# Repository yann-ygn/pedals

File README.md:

# pedals

A collection of guitar effects pcbs made with Eagle.

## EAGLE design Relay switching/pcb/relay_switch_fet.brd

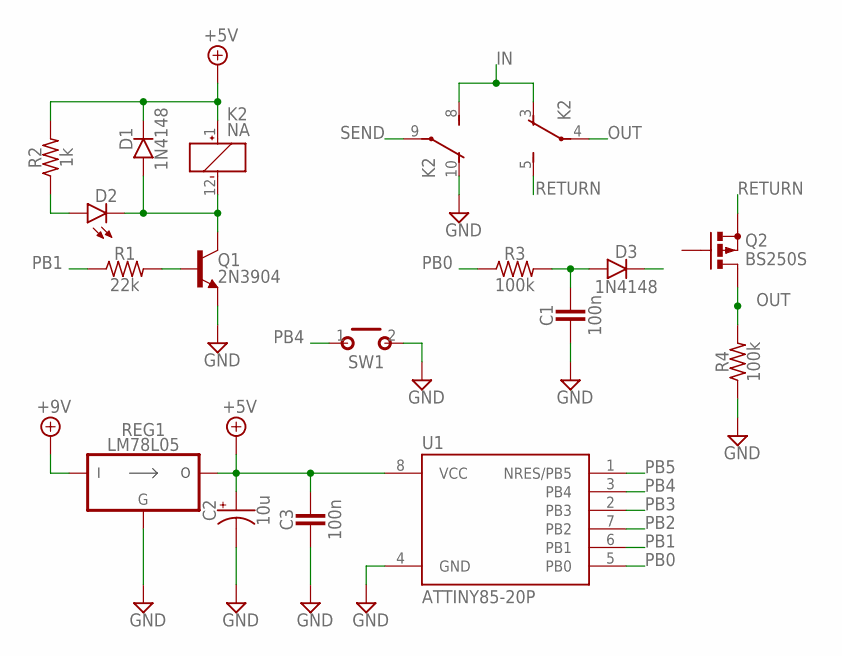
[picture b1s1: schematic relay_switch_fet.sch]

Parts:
C1: 100n; BOX_SMALL
C2: 10u; 050_020
C3: 100n; 050X030_025_2
D1, D3: 1N4148; DO35-2
D2: LED; 3MM_D
K2: NA
Q1: 2N3904; TO92-
Q2: BS250S; SOT54ES
R1: 22k; R0207/3
R2: 1k; R0207/3
R3, R4: 100k; R0207/3
REG1: LM78L05; TO92-
SW1: MOMENTARY; SPST
U1: ATTINY85-20P; PDIP08_300MIL

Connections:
+5V: C2.+, C3.1, D1.C, K2.1 (+), R2.2, REG1.3 (VO), U1.8 (VCC)
+9V: REG1.1 (VI)
GND: C1.2, C2.-, C3.2, K2.10 (O), Q1.3 (E), R4.1, REG1.2 (GND), SW1.2 (S), U1.4 (GND)
IN: K2.3 (O), K2.8 (S)
unnamed: D1.A, D2.P$1 (C), K2.12 (-), Q1.1 (C)
unnamed: Q1.2 (B), R1.2
unnamed: D2.ANODE (A), R2.1
unnamed: C1.1, D3.A, R3.2
OUT: K2.4, Q2.D, R4.2
PB0: R3.1, U1.5 (PB0)
PB1: R1.1, U1.6 (PB1)
PB2: U1.7 (PB2)
PB3: U1.2 (PB3)
PB4: SW1.1, U1.3 (PB4)
PB5: U1.1 (NRES/PB5)
RETURN: K2.5 (S), Q2.S
SEND: K2.9

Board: 2 copper layers, 15 parts (0 on the bottom side), 11 nets, no tracks yet.

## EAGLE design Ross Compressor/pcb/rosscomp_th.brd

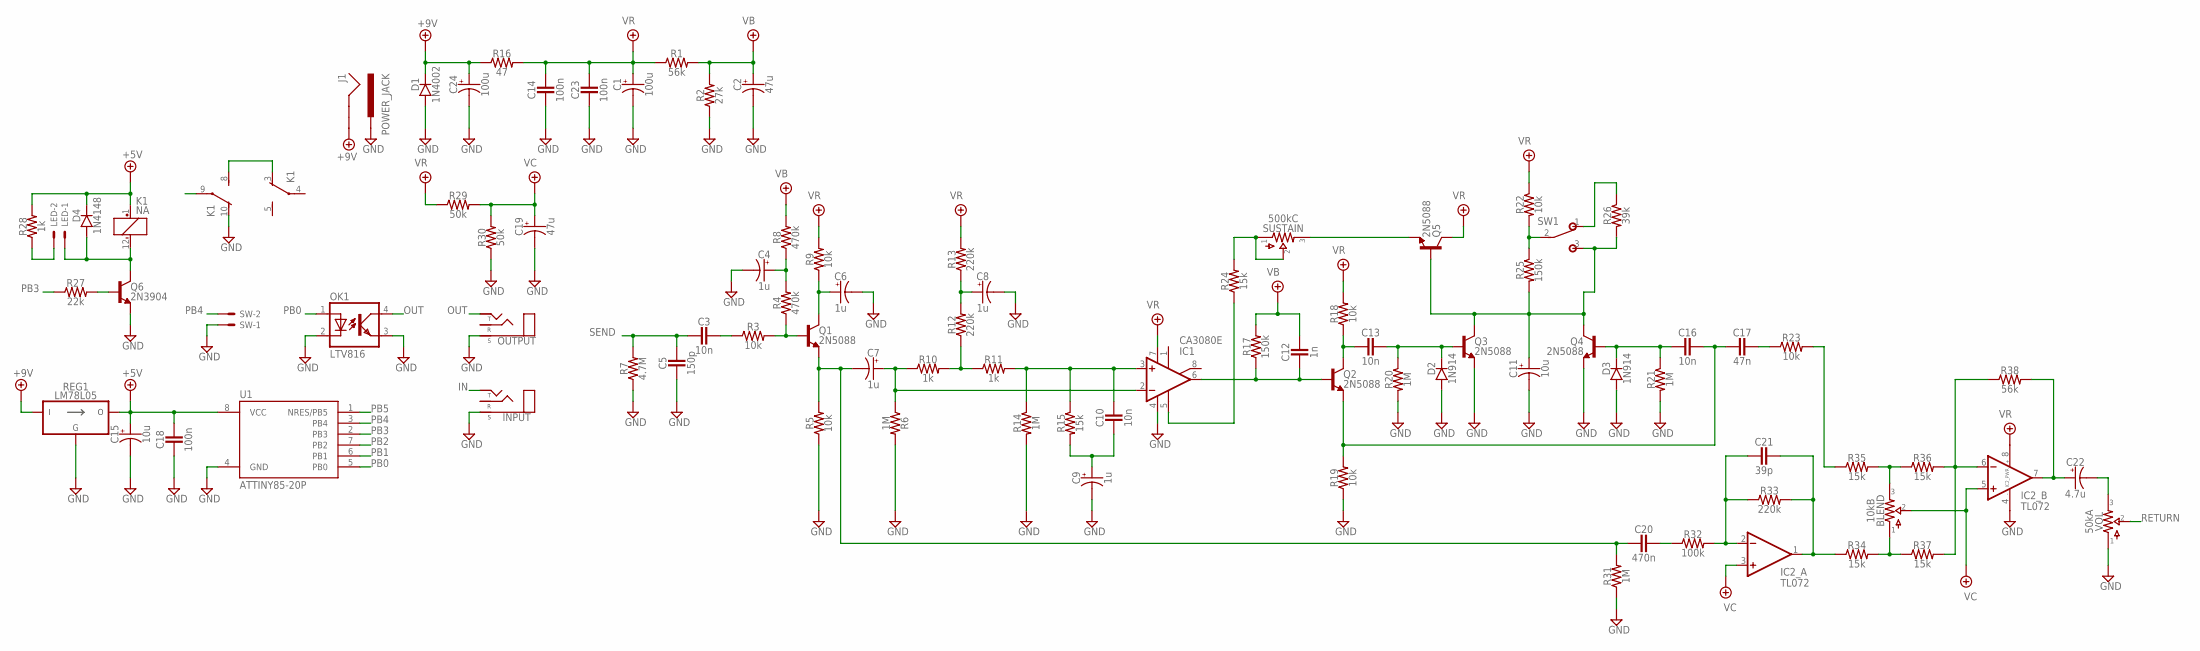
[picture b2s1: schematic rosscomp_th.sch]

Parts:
BLEND: 10kB; 16MM
C1, C24: 100u; 050_020
C2, C19: 47u; 050_020
C3, C10, C13, C16: 10n; BOX_SMALL
C4, C6, C7, C8, C9: 1u; 040_020
C5: 150p; 050X030_025_2
C11, C15: 10u; 050_020
C12: 1n; BOX_SMALL
C14, C18, C23: 100n; 050X030_025_2
C17: 47n; BOX_SMALL
C20: 470n; BOX_MED
C21: 39p; 050X030_025_2
C22: 4.7u; 050_020
D1: 1N4002; DO41-2
D2, D3: 1N914; DO35-2
D4: 1N4148; DO35-2
IC1: CA3080E; DIL0
IC2: TL072; DIL0
INPUT: STEREONMJ; NMJ6HCD2
J1: POWER_JACK; POWER_JACK_PTH
K1: NA
LED: JST-XH-02-PIN-ROUND-PAD; JST-XH-02-PACKAGE-ROUND-PAD
OK1: LTV816; DIL04
OUTPUT: STEREONMJ; NMJ6HCD2
Q1, Q2, Q3, Q4, Q5: 2N5088; TO92-
Q6: 2N3904; TO92-
R1, R38: 56k; R0207/3
R2: 27k; R0207/3
R3, R5, R9, R18, R19, R22, R23: 10k; R0207/3
R4, R8: 470k; R0207/3
R6, R14, R20, R21, R31: 1M; R0207/3
R7: 4.7M; R0207/3
R10, R11, R28: 1k; R0207/3
R12, R13, R33: 220k; R0207/3
R15, R24, R34, R35, R36, R37: 15k; R0207/3
R16: 47; R0207/3
R17, R25: 150k; R0207/3
R26: 39k; R0207/3
R27: 22k; R0207/3
R29, R30: 50k; R0207/3
R32: 100k; R0207/3
REG1: LM78L05; TO92-
SUSTAIN: 500kC; 16MM
SW: JST-XH-02-PIN-ROUND-PAD; JST-XH-02-PACKAGE-ROUND-PAD
SW1: SPDT; M9040P
U1: ATTINY85-20P; PDIP08_300MIL
VOL: 50kA; 16MM

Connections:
+5V: C15.+, C18.1, D4.C, K1.1 (+), R28.2, REG1.3 (VO), U1.8 (VCC)
+9V: C24.+, D1.C, J1.GND, R16.1, REG1.1 (VI)
GND: C1.-, C2.-, C4.-, C5.2, C6.-, C8.-, C9.-, C11.-, C14.1, C15.-, C18.2, C19.-, C23.1, C24.-, D1.A, D2.A, D3.A, IC1.4 (V-), IC2.4 (V-), INPUT.S, J1.PWR, K1.10 (O), OK1.2 (C), OK1.3 (EMIT), OUTPUT.S, Q3.3 (E), Q4.3 (E), Q6.3 (E), R2.1, R5.1, R6.2, R7.1, R14.2, R19.1, R20.2, R21.2, R30.1, R31.1, REG1.2 (GND), SW.1, U1.4 (GND), VOL.1
IN: INPUT.T
unnamed: D4.A, K1.12 (-), LED.1, Q6.1 (C)
unnamed: C3.1, R3.1
unnamed: Q1.2 (B), R3.2, R4.1
unnamed: Q6.2 (B), R27.2
unnamed: C4.+, R4.2, R8.1
unnamed: R26.1, SW1.1 (O)
unnamed: C6.+, Q1.1 (C), R9.1
unnamed: C7.+, IC1.2 (-IN), R6.1, R10.1
unnamed: C7.-, C20.2, Q1.3 (E), R5.2, R31.2
unnamed: C10.1, IC1.3 (+IN), R11.2, R14.1, R15.1
unnamed: R10.2, R11.1, R12.1
unnamed: C8.+, R12.2, R13.1
unnamed: C9.+, C10.2, R15.2
unnamed: C13.2, Q2.1 (C), R18.1
unnamed: C12.2, IC1.6 (OUT), Q2.2 (B), R17.1
unnamed: C16.1, C17.2, Q2.3 (E), R19.2
unnamed: C13.1, D2.C, Q3.2 (B), R20.1
unnamed: C11.+, Q3.1 (C), Q4.1 (C), Q5.2 (B), R25.2, R26.2, SW1.3 (S)
unnamed: C16.2, D3.C, Q4.2 (B), R21.1
unnamed: R22.2, R25.1, SW1.2
unnamed: C17.1, R23.1
unnamed: C20.1, R32.1
unnamed: Q5.3 (E), SUSTAIN.3
unnamed: LED.2, R28.1
unnamed: R24.2, SUSTAIN.1, SUSTAIN.2
unnamed: IC1.5 (OPT), R24.1
unnamed: K1.3 (O), K1.8 (S)
unnamed: C21.2, IC2.2 (-IN), R32.2, R33.1
unnamed: C21.1, IC2.1 (OUT), R33.2, R34.1
unnamed: BLEND.1, R34.2, R37.1
unnamed: BLEND.3, R35.2, R36.1
unnamed: R23.2, R35.1
unnamed: C22.+, IC2.7 (OUT), R38.2
unnamed: C22.-, VOL.3
unnamed: IC2.6 (-IN), R36.2, R37.2, R38.1
OUT: OK1.4 (COL), OUTPUT.T
PB0: OK1.1 (A), U1.5 (PB0)
PB1: U1.6 (PB1)
PB2: U1.7 (PB2)
PB3: R27.1, U1.2 (PB3)
PB4: SW.2, U1.3 (PB4)
PB5: U1.1 (NRES/PB5)
RETURN: VOL.2
SEND: C3.2, C5.1, R7.2
VB: C2.+, C12.1, R1.2, R2.2, R8.2, R17.2
VC: BLEND.2, C19.+, IC2.3 (+IN), IC2.5 (+IN), R29.2, R30.2
VR: C1.+, C14.2, C23.2, IC1.7 (V+), IC2.8 (V+), Q5.1 (C), R1.1, R9.2, R13.2, R16.2, R18.2, R22.1, R29.1

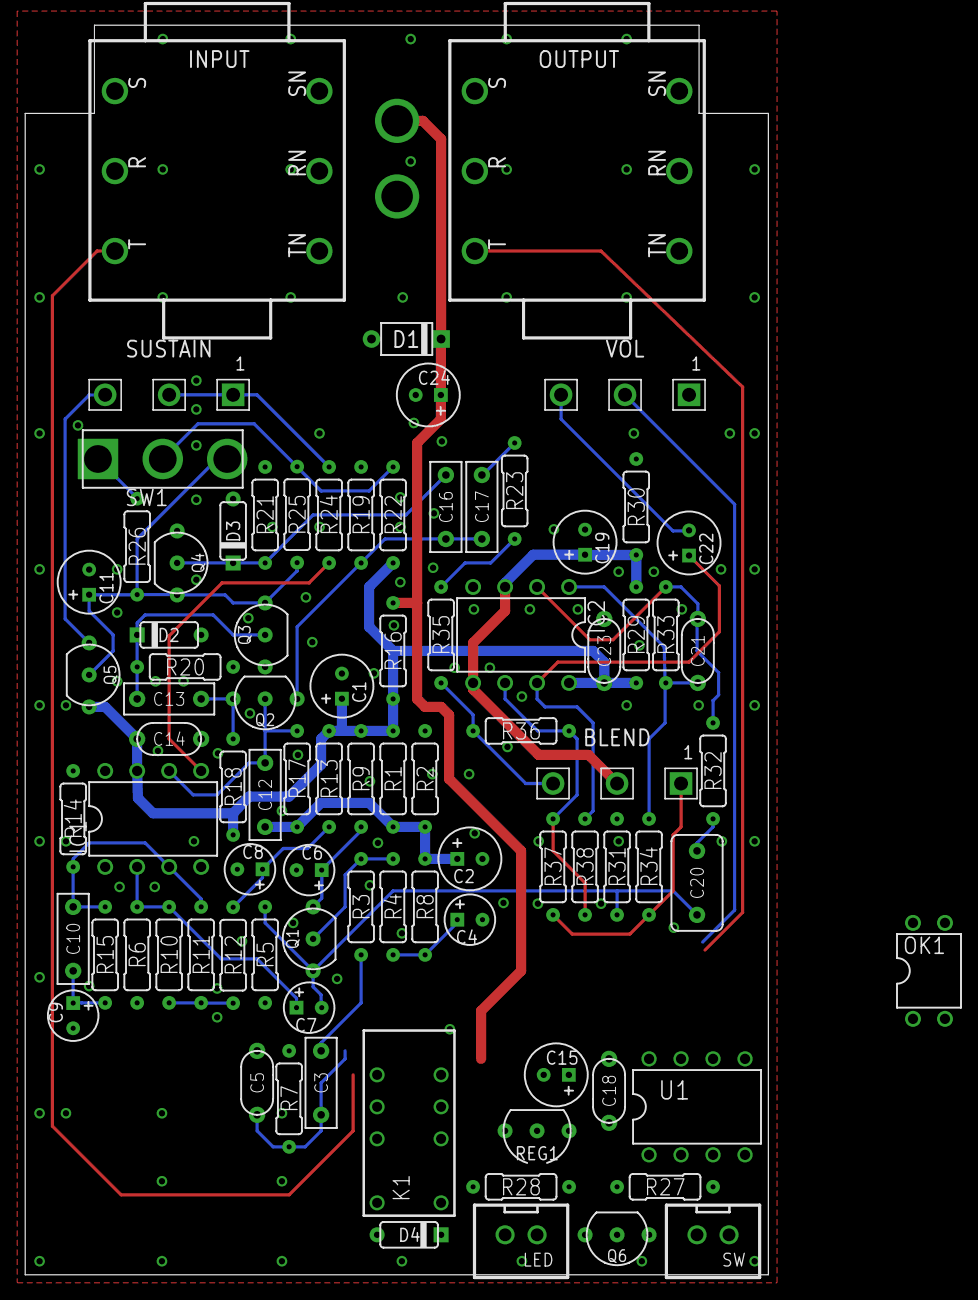
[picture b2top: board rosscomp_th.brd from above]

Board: 2 copper layers, 59.0 x 99.2 mm, 88 parts (1 on the bottom side), 46 nets.

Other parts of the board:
U$2: 125B_PCB_HUGER

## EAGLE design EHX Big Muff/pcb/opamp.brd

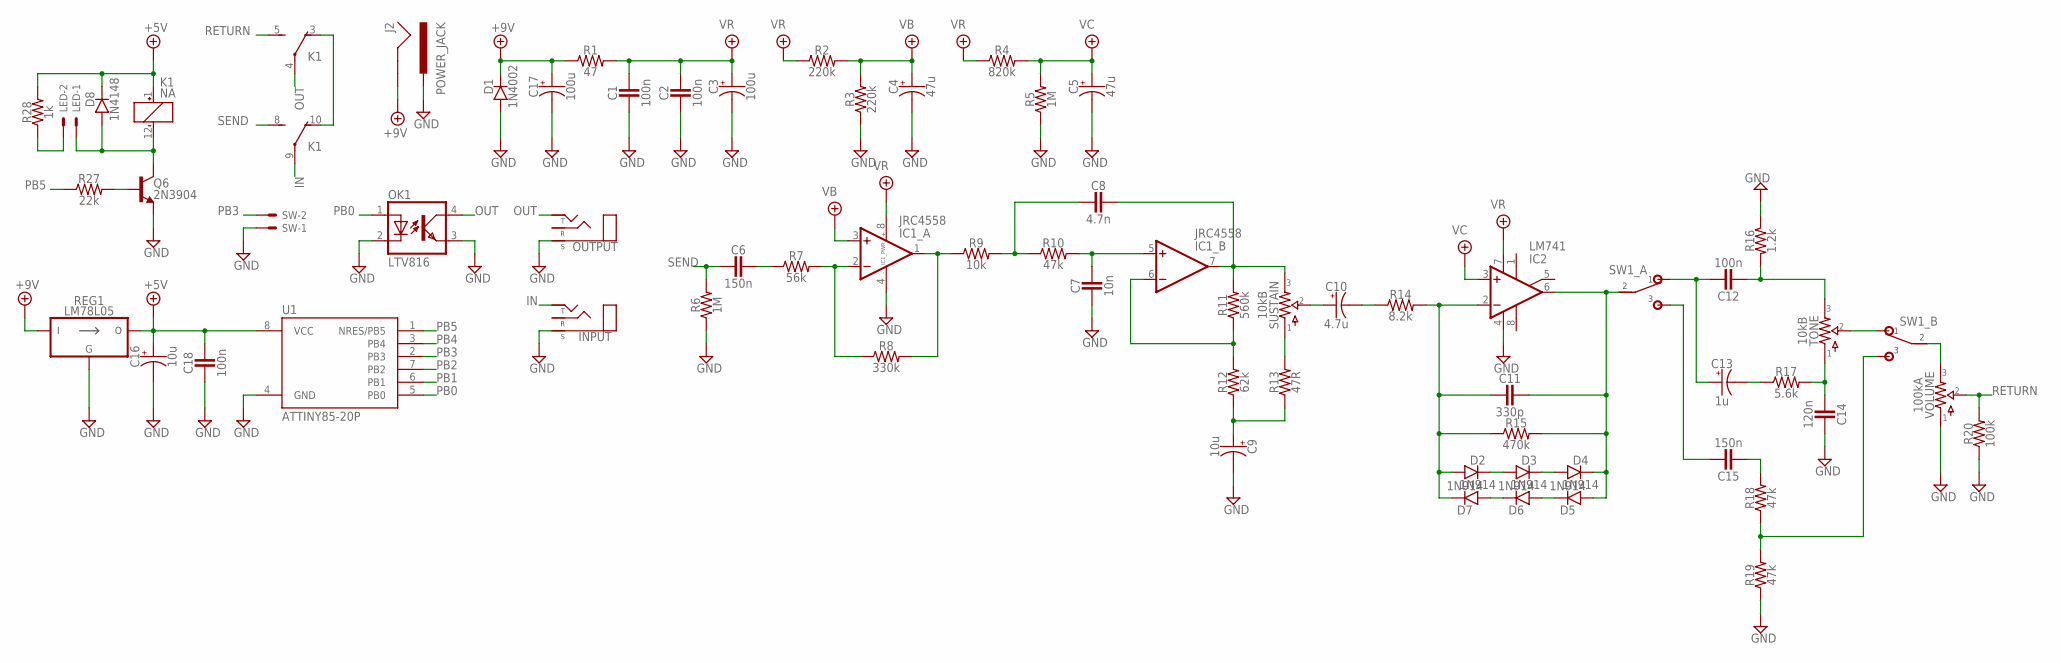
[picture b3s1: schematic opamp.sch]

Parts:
C1, C2, C18: 100n; 050X030_025_2
C3, C17: 100u; 050_020
C4, C5: 47u; 050_020
C6, C15: 150n; BOX_SMALL
C7: 10n; BOX_SMALL
C8: 4.7n; BOX_SMALL
C9, C16: 10u; 050_020
C10: 4.7u; 050_020
C11: 330p; 050X030_025_2
C12: 100n; BOX_SMALL
C13: 1u; 040_020
C14: 120n; 050X030_025_2
D1: 1N4002; DO41-2
D2, D3, D4, D5, D6, D7: 1N914; DO35-2
D8: 1N4148; DO35-2
IC1: JRC4558; DIL0
IC2: LM741; DIL0
INPUT: STEREONMJ; NMJ6HCD2
J2: POWER_JACK; POWER_JACK_PTH
K1: NA
LED: JST-XH-02-PIN-ROUND-PAD; JST-XH-02-PACKAGE-ROUND-PAD
OK1: LTV816; DIL04
OUTPUT: STEREONMJ; NMJ6HCD2
Q6: 2N3904; TO92-
R1: 47; R0207/3
R2, R3: 220k; R0207/3
R4: 820k; R0207/3
R5, R6: 1M; R0207/3
R7: 56k; R0207/3
R8: 330k; R0207/3
R9: 10k; R0207/3
R10, R18, R19: 47k; R0207/3
R11: 560k; R0207/3
R12: 62k; R0207/3
R13: 47R; R0207/3
R14: 8.2k; R0207/3
R15: 470k; R0207/3
R16: 1.2k; R0207/3
R17: 5.6k; R0207/3
R20: 100k; R0207/3
R27: 22k; R0207/3
R28: 1k; R0207/3
REG1: LM78L05; TO92-
SUSTAIN: 10kB; 16MM
SW: JST-XH-02-PIN-ROUND-PAD; JST-XH-02-PACKAGE-ROUND-PAD
SW1: DPDT
TONE: 10kB; 16MM
U1: ATTINY85-20P; PDIP08_300MIL
VOLUME: 100kA; 16MM

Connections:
+5V: C16.+, C18.1, D8.C, K1.1 (+), R28.2, REG1.3 (VO), U1.8 (VCC)
+18V: C17.+, D1.C, J2.GND, R1.1, REG1.1 (VI)
GND: C1.1, C2.1, C3.-, C4.-, C5.-, C7.1, C9.-, C14.1, C16.-, C17.-, C18.2, D1.A, IC1.4 (V-), IC2.4 (V-), INPUT.S, J2.PWR, OK1.2 (C), OK1.3 (EMIT), OUTPUT.S, Q6.3 (E), R3.1, R5.1, R6.1, R16.1, R19.1, R20.1, REG1.2 (GND), SW.1, U1.4 (GND), VOLUME.1
IN: INPUT.T, K1.9
unnamed: D8.A, K1.12 (-), LED.1, Q6.1 (C)
unnamed: Q6.2 (B), R27.2
unnamed: C6.2, R7.1
unnamed: IC1.2 (-IN), R7.2, R8.1
unnamed: IC1.1 (OUT), R8.2, R9.1
unnamed: C8.2, R9.2, R10.1
unnamed: C7.2, IC1.5 (+IN), R10.2
unnamed: C8.1, IC1.7 (OUT), R11.2, SUSTAIN.3
unnamed: IC1.6 (-IN), R11.1, R12.2
unnamed: C9.+, R12.1, R13.1
unnamed: R13.2, SUSTAIN.1
unnamed: C10.+, SUSTAIN.2
unnamed: C10.-, R14.1
unnamed: C11.2, D2.A, D7.C, IC2.2 (-IN), R14.2, R15.1
unnamed: D2.C, D3.A
unnamed: D3.C, D4.A
unnamed: D6.C, D7.A
unnamed: D5.C, D6.A
unnamed: C11.1, D4.C, D5.A, IC2.6 (OUT), R15.2, SW1.A2 (2)
unnamed: C13.-, R17.1
unnamed: C14.2, R17.2, TONE.1
unnamed: C12.2, R16.2, TONE.3
unnamed: C15.2, R18.2
unnamed: R18.1, R19.2, SW1.B3 (3)
unnamed: SW1.B1 (1), TONE.2
unnamed: SW1.B2 (2), VOLUME.3
unnamed: LED.2, R28.1
unnamed: C12.1, C13.+, SW1.A1 (1)
unnamed: C15.1, SW1.A3 (3)
unnamed: K1.3 (O), K1.10 (O)
OUT: K1.4, OK1.4 (COL), OUTPUT.T
PB0: OK1.1 (A), U1.5 (PB0)
PB1: U1.6 (PB1)
PB2: U1.7 (PB2)
PB3: SW.2, U1.2 (PB3)
PB4: U1.3 (PB4)
PB5: R27.1, U1.1 (NRES/PB5)
RETURN: K1.5 (S), R20.2, VOLUME.2
SEND: C6.1, K1.8 (S), R6.2
VB: C4.+, IC1.3 (+IN), R2.2, R3.2
VC: C5.+, IC2.3 (+IN), R4.2, R5.2
VR: C1.2, C2.2, C3.+, IC1.8 (V+), IC2.7 (V+), R1.2, R2.1, R4.1

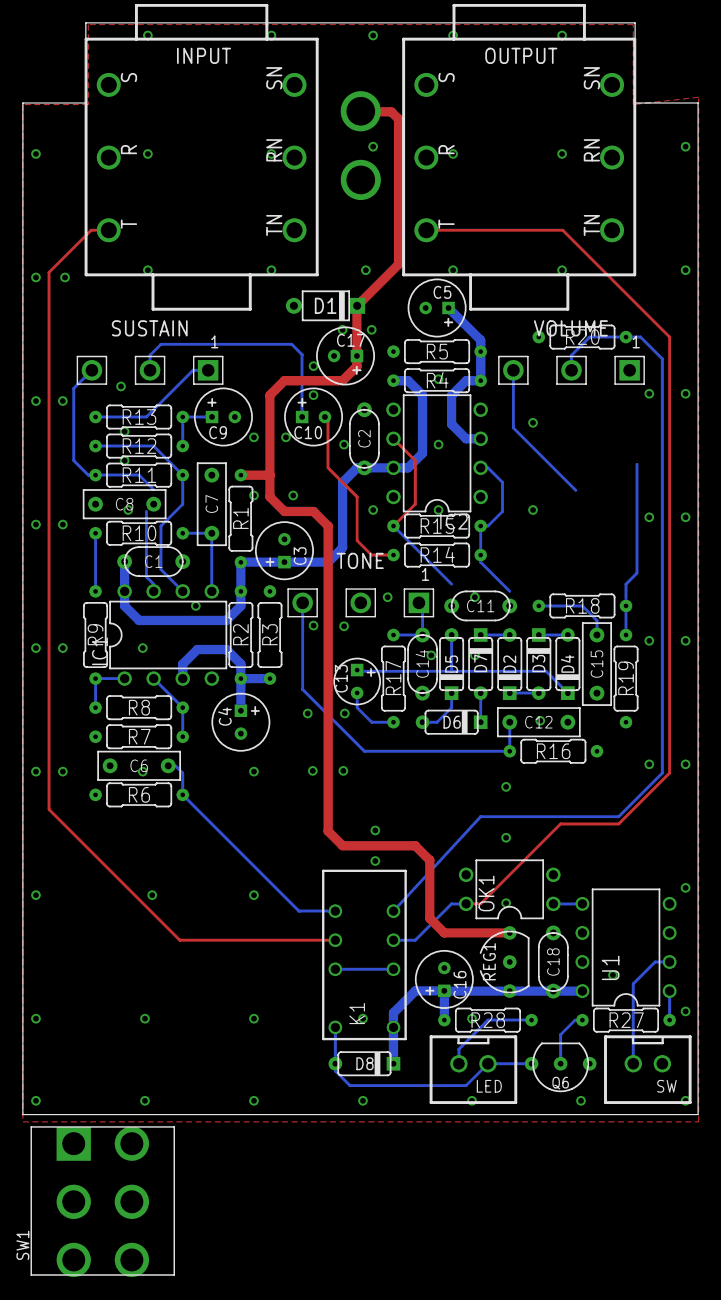
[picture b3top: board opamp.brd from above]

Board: 2 copper layers, 59.0 x 95.4 mm, 65 parts (1 on the bottom side), 43 nets.

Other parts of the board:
U$1: 125B_PCB_HUGER

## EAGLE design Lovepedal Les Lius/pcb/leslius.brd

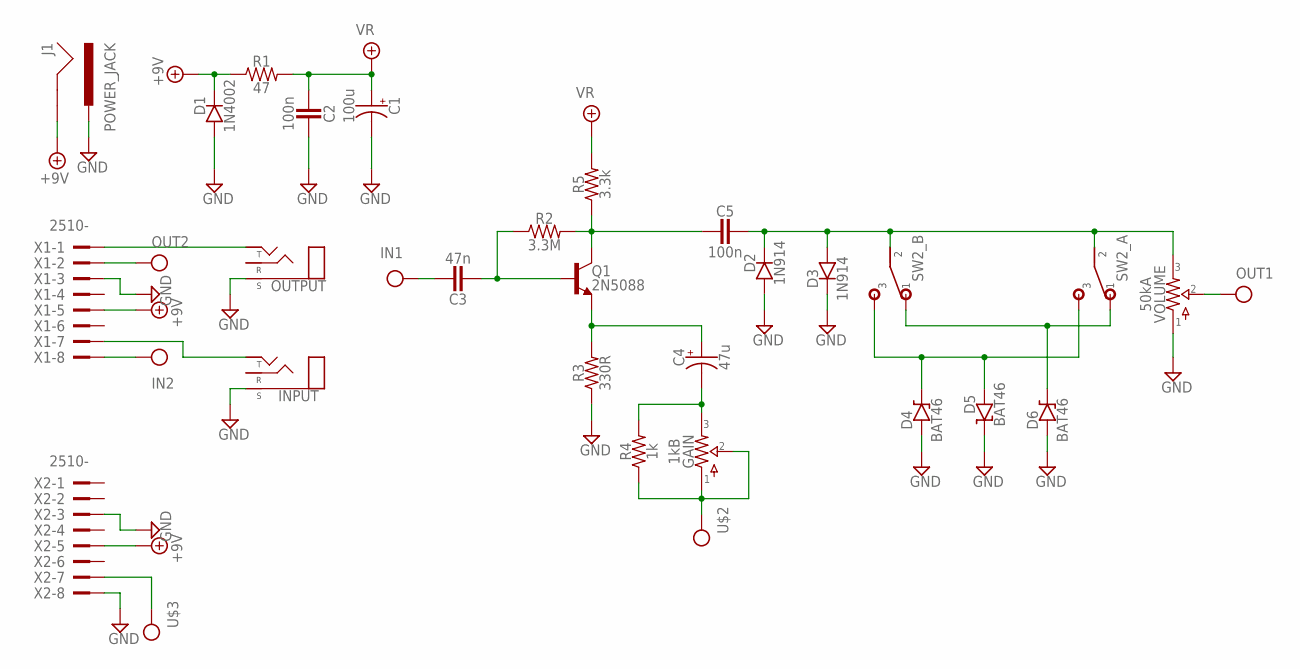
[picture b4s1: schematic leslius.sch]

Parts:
C1: 100u; 040_020
C2: 100n; 050X030_025_2
C3: 47n; BOX_SMALL
C4: 47u; 040_020
C5: 100n; BOX_SMALL
D1: 1N4002; DO41-2
D2, D3: 1N914; DO35-2
D4, D5, D6: BAT46; DO41-2
GAIN: 1kB; 16MM
INPUT: STEREONMJ; NMJ6HCD2
J1: POWER_JACK; POWER_JACK_PTH
OUTPUT: STEREONMJ; NMJ6HCD2
Q1: 2N5088; TO92-
R1: 47; R0207/3
R2: 3.3M; R0207/3
R3: 330R; R0207/3
R4: 1k; R0207/3
R5: 3.3k; R0207/3
SW2: DPDT
VOLUME: 50kA; 16MM
X1, X2: 2510-; PAK100/2500-10

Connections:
+9V: D1.C, J1.GND, R1.1, X1.5, X2.5
GND: C1.-, C2.1, D1.A, D2.A, D3.C, D4.A, D5.C, D6.A, INPUT.S, J1.PWR, OUTPUT.S, R3.1, VOLUME.1, X1.3, X2.3, X2.8
IN: C3.1, X1.8
unnamed: C3.2, Q1.2 (B), R2.1
unnamed: INPUT.T, X1.7
unnamed: C5.1, Q1.1 (C), R2.2, R5.1
unnamed: OUTPUT.T, X1.1
unnamed: C4.+, Q1.3 (E), R3.2
unnamed: C4.-, GAIN.3, R4.2
unnamed: D6.C, SW2.A1 (1), SW2.B1 (1)
unnamed: D4.C, D5.A, SW2.A3 (3), SW2.B3 (3)
unnamed: C5.2, D2.C, D3.A, SW2.A2 (2), SW2.B2 (2), VOLUME.3
OUT: VOLUME.2, X1.2
SND: GAIN.1, GAIN.2, R4.1, X2.7
VR: C1.+, C2.2, R1.2, R5.2

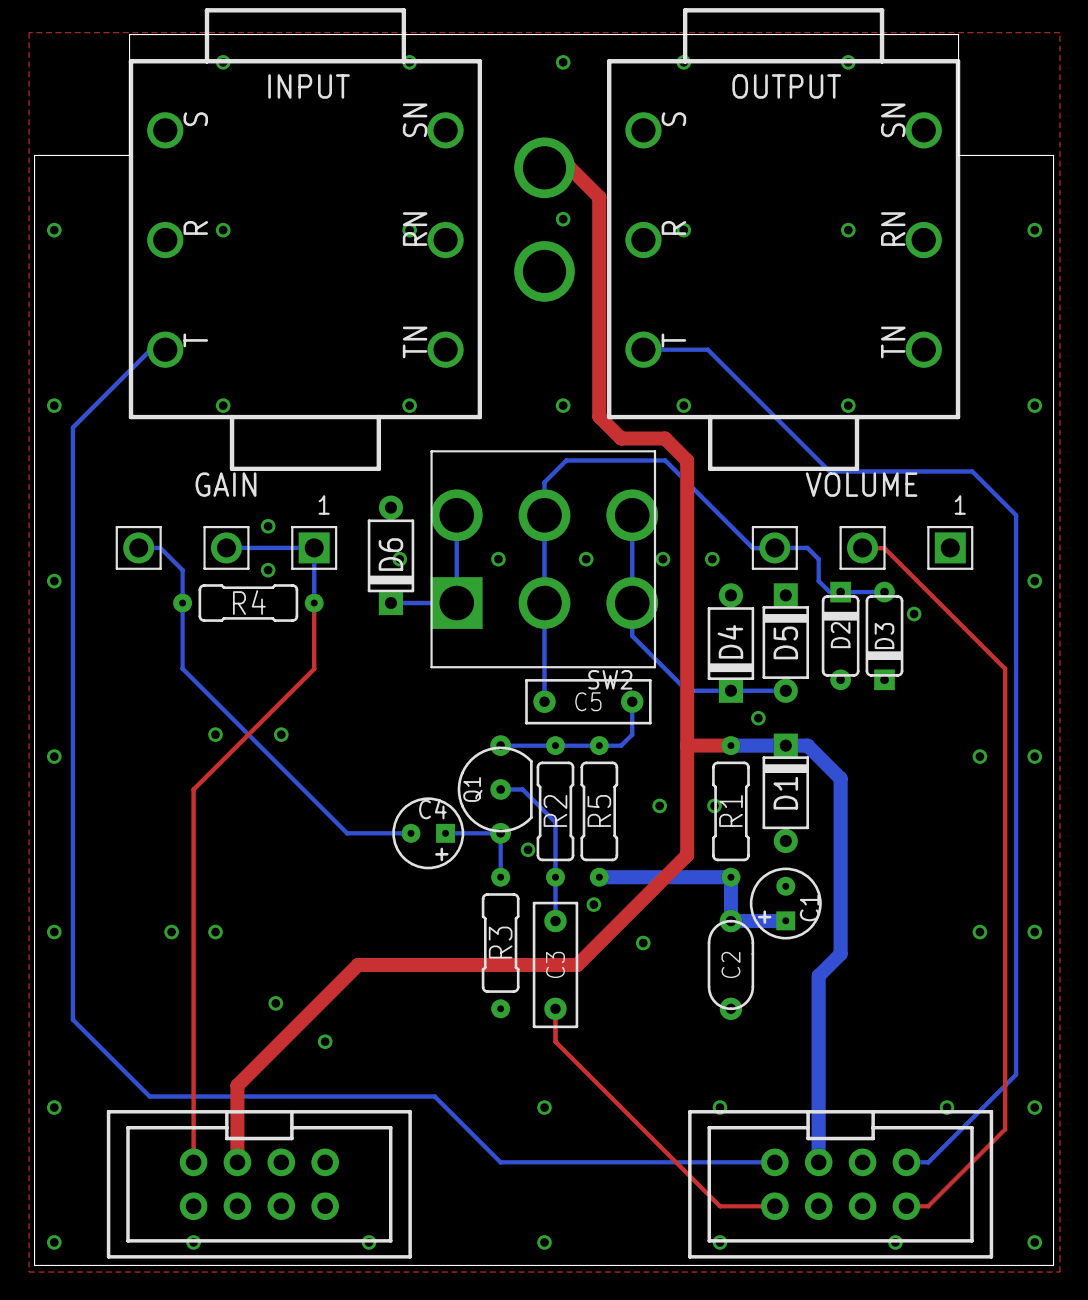
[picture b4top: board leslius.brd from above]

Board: 2 copper layers, 59.0 x 71.3 mm, 26 parts (1 on the bottom side), 15 nets.

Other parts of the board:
U$1: 125B_PCB

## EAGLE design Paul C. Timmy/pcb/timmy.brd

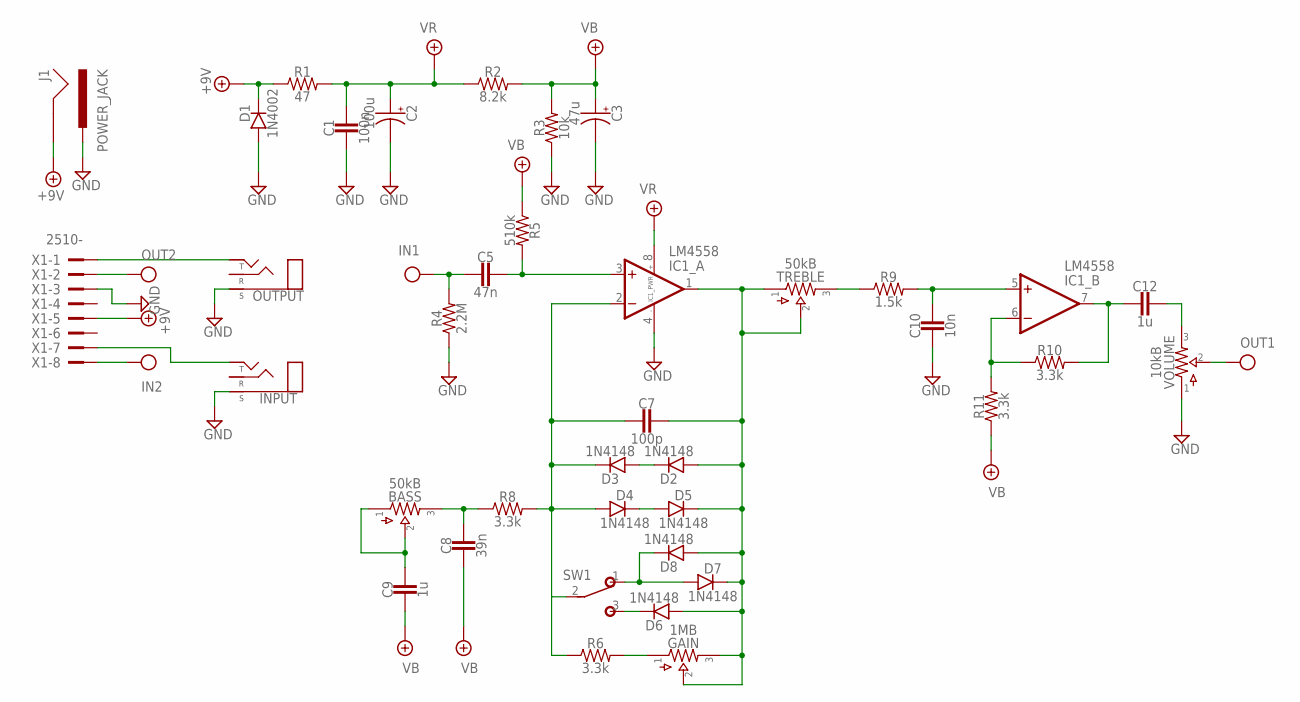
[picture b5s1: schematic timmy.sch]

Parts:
BASS: 50kB; 16MM
C1: 100n; 050X030_025_2
C2: 100u; 050_020
C3: 47u; 050_020
C5: 47n; BOX_SMALL
C7: 100p; 050X030_025_2
C8: 39n; BOX_SMALL
C9, C12: 1u; BOX_BIG
C10: 10n; BOX_SMALL
D1: 1N4002; DO41-2
D2, D3, D4, D5, D6, D7, D8: 1N4148; DO35-2
GAIN: 1MB; 16MM
IC1: LM4558; DIL08
INPUT: STEREONMJ; NMJ6HCD2
J1: POWER_JACK; POWER_JACK_PTH
OUTPUT: STEREONMJ; NMJ6HCD2
R1: 47; R0207/3
R2: 8.2k; R0207/3
R3: 10k; R0207/3
R4: 2.2M; R0207/3
R5: 510k; R0207/3
R6, R8, R10, R11: 3.3k; R0207/3
R9: 1.5k; R0207/3
SW1: SPDT; M9040P
TREBLE: 50kB; 16MM
VOLUME: 10kB; 16MM
X1: 2510-; PAK100/2500-10

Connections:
+9V: D1.C, J1.GND, R1.1, X1.5
GND: C1.2, C2.-, C3.-, C10.2, D1.A, IC1.4 (V-), INPUT.S, J1.PWR, OUTPUT.S, R3.1, R4.1, VOLUME.1, X1.3
IN: C5.2, R4.2, X1.8
unnamed: D6.C, SW1.3 (S)
unnamed: INPUT.T, X1.7
unnamed: C5.1, IC1.3 (+IN), R5.2
unnamed: OUTPUT.T, X1.1
unnamed: C7.2, D3.C, D4.A, IC1.2 (-IN), R6.1, R8.2, SW1.2
unnamed: C7.1, D2.A, D5.C, D6.A, D7.C, D8.A, GAIN.2, GAIN.3, IC1.1 (OUT), TREBLE.1, TREBLE.2
unnamed: GAIN.1, R6.2
unnamed: D2.C, D3.A
unnamed: D4.C, D5.A
unnamed: D7.A, D8.C, SW1.1 (O)
unnamed: BASS.3, C8.1, R8.1
unnamed: R9.1, TREBLE.3
unnamed: BASS.1, BASS.2, C9.1
unnamed: C10.1, IC1.5 (+IN), R9.2
unnamed: IC1.6 (-IN), R10.1, R11.2
unnamed: C12.2, IC1.7 (OUT), R10.2
unnamed: C12.1, VOLUME.3
OUT: VOLUME.2, X1.2
VB: C3.+, C8.2, C9.2, R2.2, R3.2, R5.1, R11.1
VR: C1.1, C2.+, IC1.8 (V+), R1.2, R2.1

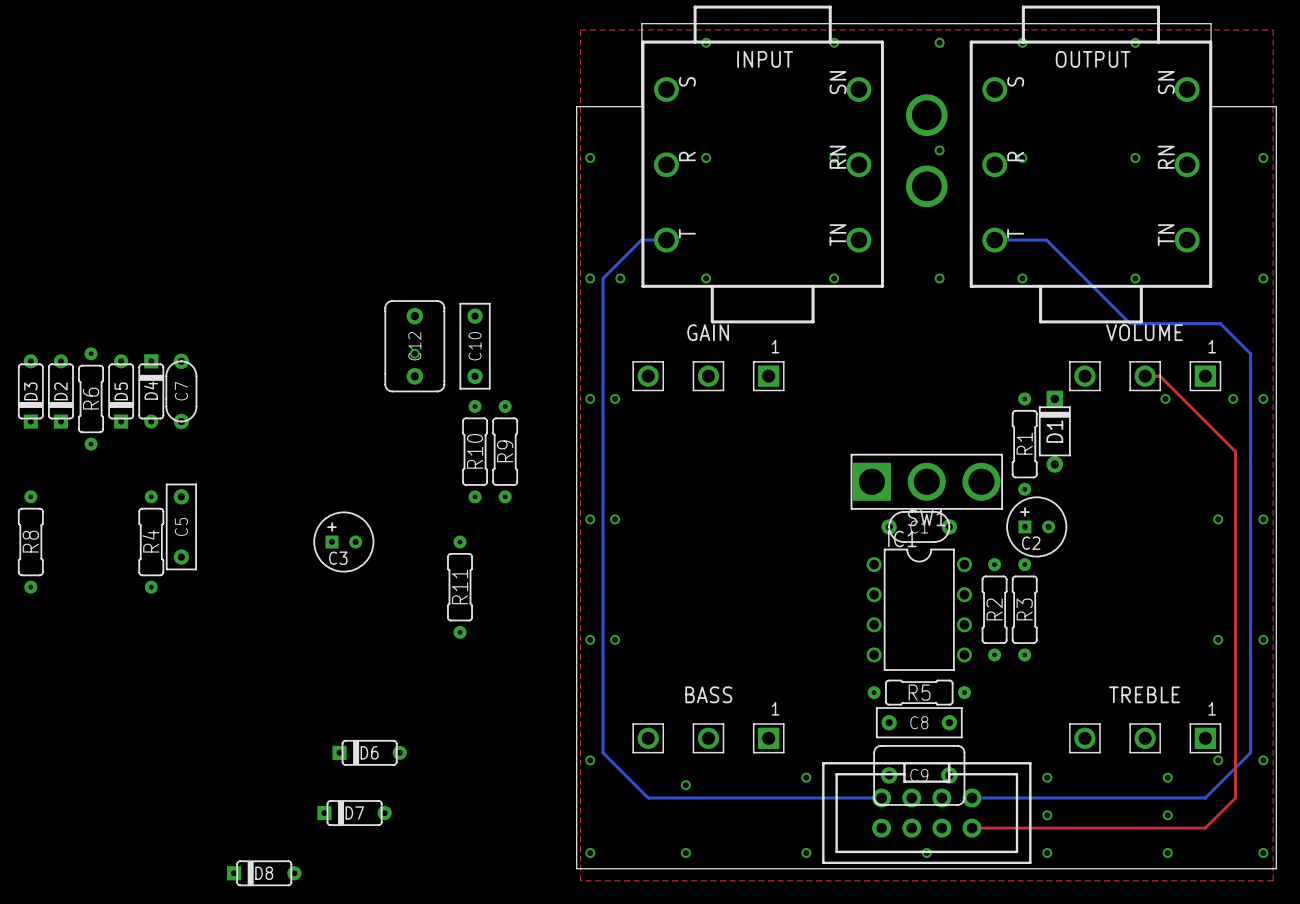
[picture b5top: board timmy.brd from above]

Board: 2 copper layers, 59.0 x 71.3 mm, 38 parts (1 on the bottom side), 23 nets.

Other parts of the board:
U$1: 125B_PCB

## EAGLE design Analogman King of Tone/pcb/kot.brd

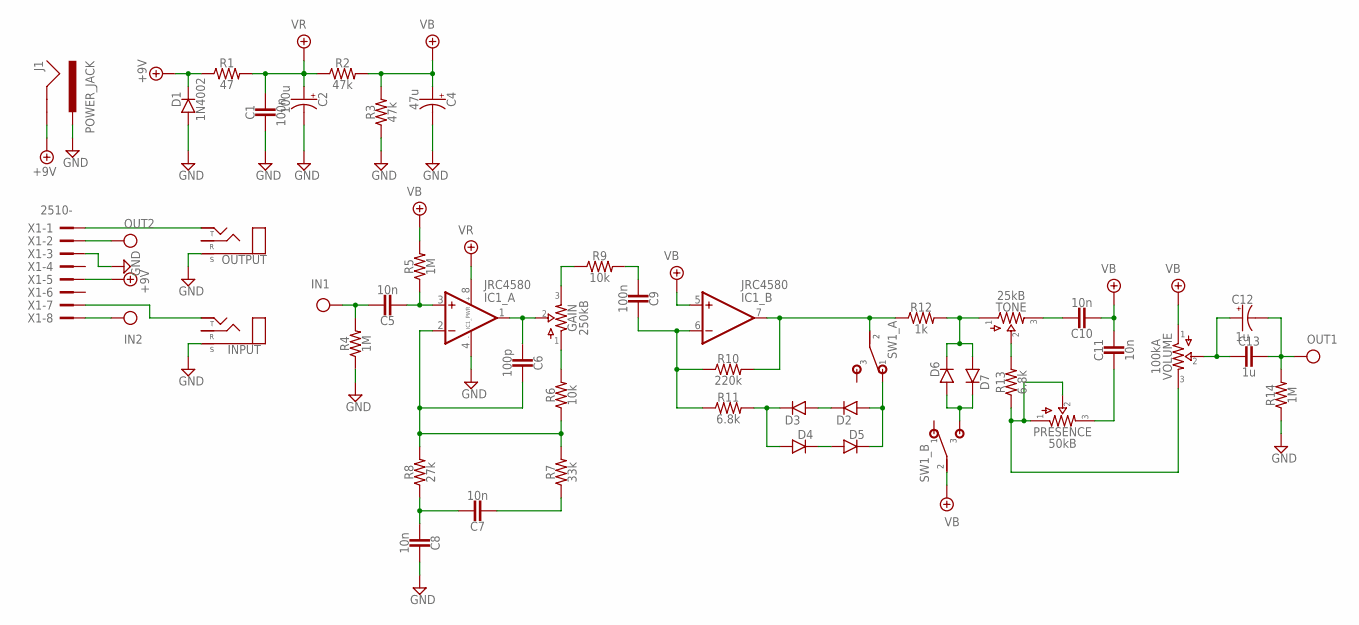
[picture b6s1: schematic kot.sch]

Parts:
C1: 100n; 050X030_025_2
C2: 100u; 050_020
C4: 47u; 050_020
C5, C7, C8, C10, C11: 10n; BOX_SMALL
C6: 100p; 050X030_025_2
C9: 100n; BOX_SMALL
C12: 1u; 040_020
C13: 1u; BOX_BIG
D1: 1N4002; DO41-2
D2, D3, D4, D5, D6, D7: DO35.2; DO35-2
GAIN: 250kB; 16MM
IC1: JRC4580; DIL08
INPUT: STEREONMJ; NMJ6HCD2
J1: POWER_JACK; POWER_JACK_PTH
OUTPUT: STEREONMJ; NMJ6HCD2
PRESENCE: 50kB; 16MM
R1: 47; R0207/3
R2, R3: 47k; R0207/3
R4, R5, R14: 1M; R0207/3
R6, R9: 10k; R0207/3
R7: 33k; R0207/3
R8: 27k; R0207/3
R10: 220k; R0207/3
R11, R13: 6.8k; R0207/3
R12: 1k; R0207/3
SW1: DPDT
TONE: 25kB; 16MM
VOLUME: 100kA; 16MM
X1: 2510-; PAK100/2500-10

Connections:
+9V: D1.C, J1.GND, R1.1, X1.5
GND: C1.2, C2.-, C4.-, C8.1, D1.A, IC1.4 (V-), INPUT.S, J1.PWR, OUTPUT.S, R3.1, R4.1, R14.1, X1.3
IN: C5.1, R4.2, X1.8
unnamed: C5.2, IC1.3 (+IN), R5.1
unnamed: INPUT.T, X1.7
unnamed: C6.1, IC1.2 (-IN), R6.1, R7.2, R8.2
unnamed: OUTPUT.T, X1.1
unnamed: C6.2, GAIN.2, IC1.1 (OUT)
unnamed: GAIN.1, R6.2
unnamed: C7.1, C8.2, R8.1
unnamed: C7.2, R7.1
unnamed: GAIN.3, R9.1
unnamed: C9.2, R9.2
unnamed: C9.1, IC1.6 (-IN), R10.1, R11.1
unnamed: D3.C, D4.A, R11.2
unnamed: D2.C, D3.A
unnamed: D4.C, D5.A
unnamed: D2.A, D5.C, SW1.A1 (1)
unnamed: D6.A, D7.C, SW1.B3 (3)
unnamed: IC1.7 (OUT), R10.2, R12.1, SW1.A2 (2)
unnamed: D6.C, D7.A, R12.2, TONE.1
unnamed: R13.2, TONE.2
unnamed: PRESENCE.1, PRESENCE.2, R13.1, VOLUME.3
unnamed: C10.1, TONE.3
unnamed: C11.2, PRESENCE.3
unnamed: C12.+, C13.2, VOLUME.2
OUT: C12.-, C13.1, R14.2, X1.2
VB: C4.+, C10.2, C11.1, IC1.5 (+IN), R2.2, R3.2, R5.2, SW1.B2 (2), VOLUME.1
VR: C1.1, C2.+, IC1.8 (V+), R1.2, R2.1

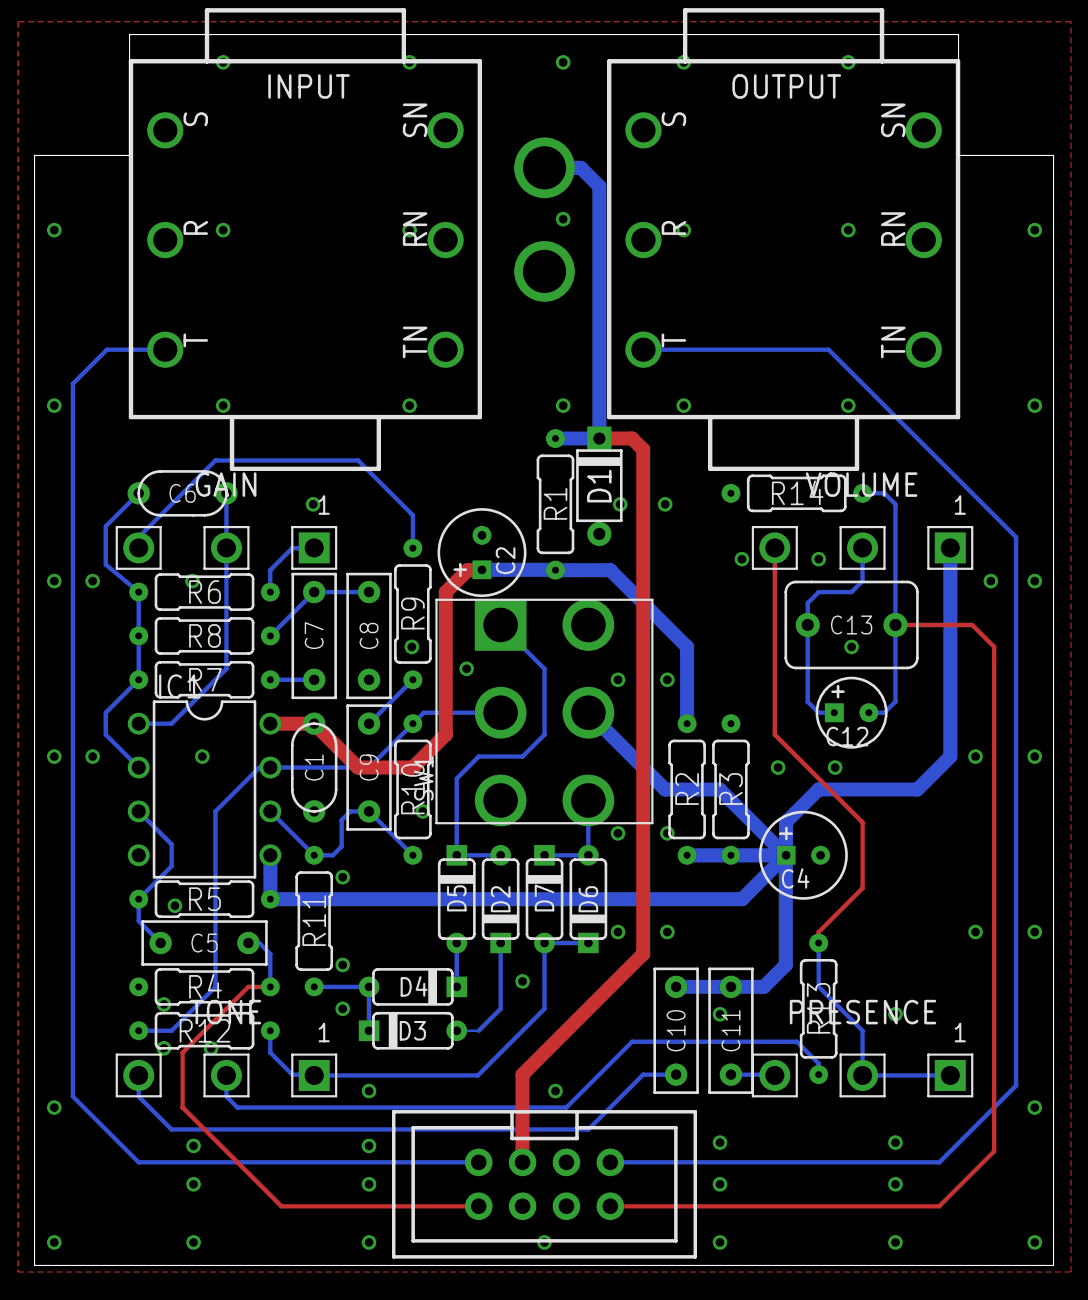
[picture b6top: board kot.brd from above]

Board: 2 copper layers, 59.0 x 71.3 mm, 44 parts (1 on the bottom side), 29 nets.

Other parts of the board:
U$1: 125B_PCB

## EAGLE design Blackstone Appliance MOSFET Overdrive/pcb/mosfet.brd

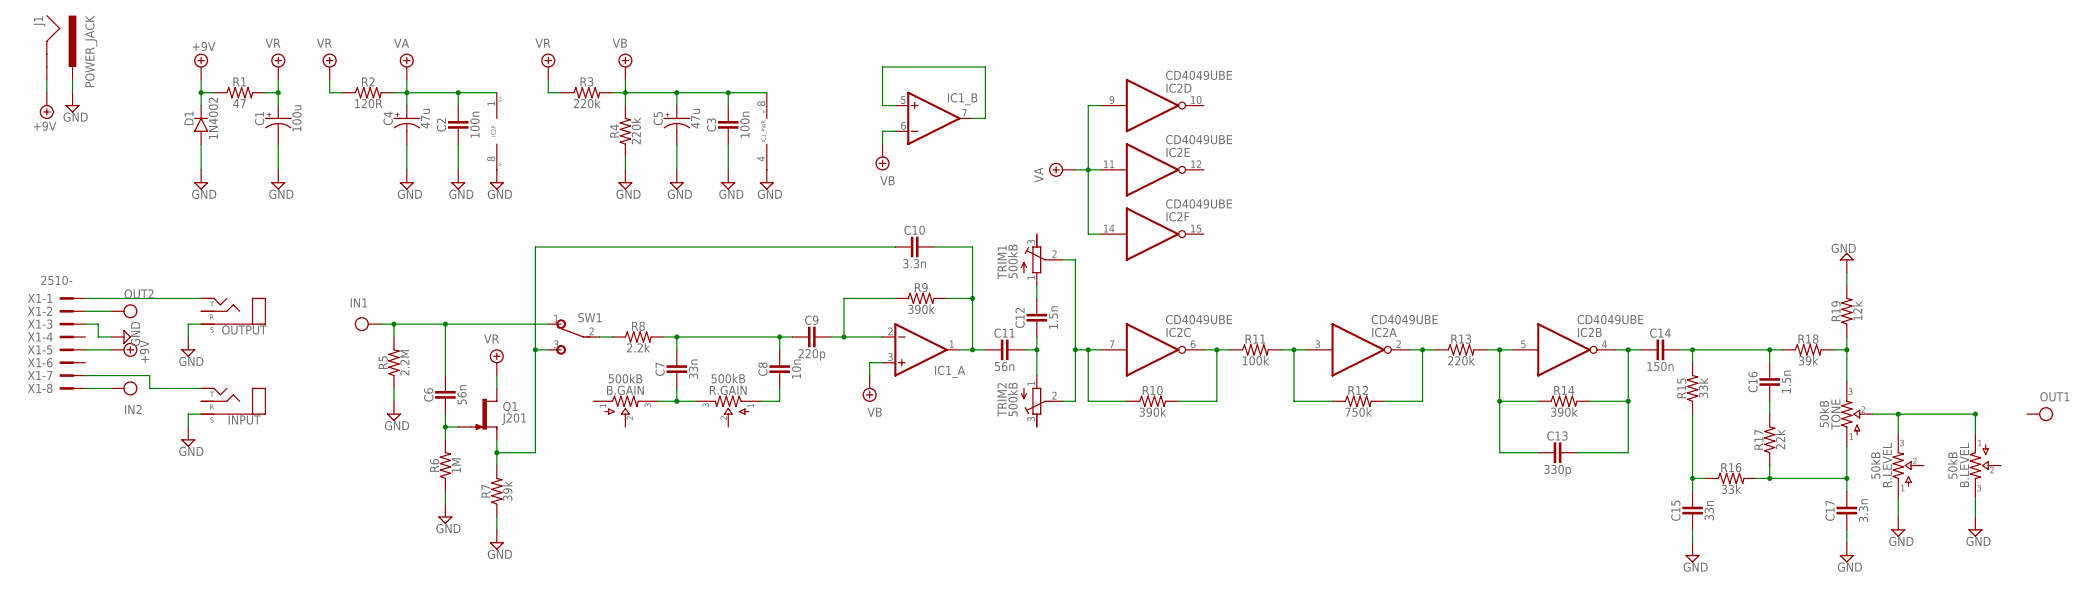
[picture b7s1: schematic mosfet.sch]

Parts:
B.GAIN: 500kB; 16MM
B.LEVEL: 50kB; 16MM
C1: 100u; 050_020
C2, C3: 100n; 050X030_025_2
C4, C5: 47u; 050_020
C6: 56n; BOX_SMALL
C7: 33n; BOX_SMALL
C8: 10n; BOX_SMALL
C9: 220p; 050X030_025_2
C10, C17: 3.3n; 050X030_025_2
C11: 56n; 050X030_025_2
C12, C16: 1.5n; 050X030_025_2
C13: 330p; 050X030_025_2
C14: 150n; 050X030_025_2
C15: 33n; 050X030_025_2
D1: 1N4002; DO41-2
IC1: DUALTH; DIL0
IC2: CD4049UBE; DIL16
INPUT: STEREONMJ; NMJ6HCD2
J1: POWER_JACK; POWER_JACK_PTH
OUTPUT: STEREONMJ; NMJ6HCD2
Q1: J201; TO92-
R1: 47; R0207/3
R2: 120R; R0207/3
R3, R4, R13: 220k; R0207/3
R5: 2.2M; R0207/3
R6: 1M; R0207/3
R7, R18: 39k; R0207/3
R8: 2.2k; R0207/3
R9, R10, R14: 390k; R0207/3
R11: 100k; R0207/3
R12: 750k; R0207/3
R15, R16: 33k; R0207/3
R17: 22k; R0207/3
R19: 12k; R0207/3
R.GAIN: 500kB; 16MM
R.LEVEL: 50kB; 16MM
SW1: SPDT; M9040P
TONE: 50kB; 16MM
TRIM1, TRIM2: 500kB; RTRIM3296W
X1: 2510-; PAK100/2500-10

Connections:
+9V: D1.C, J1.GND, R1.1, X1.5
GND: B.LEVEL.3, C1.-, C2.1, C3.1, C4.-, C5.-, C15.1, C17.1, D1.A, IC1.4 (V-), IC2.8 (VSS), INPUT.S, J1.PWR, OUTPUT.S, R4.1, R5.1, R6.1, R7.1, R19.2, R.LEVEL.1, X1.3
IN: C6.2, R5.2, SW1.1 (O), X1.8
unnamed: INPUT.T, X1.7
unnamed: C6.1, Q1.1 (G), R6.2
unnamed: C10.1, Q1.2 (S), R7.2, SW1.3 (S)
unnamed: OUTPUT.T, X1.1
unnamed: R8.1, SW1.2
unnamed: C7.2, C8.2, C9.1, R8.2
unnamed: B.GAIN.3, C7.1, R.GAIN.3
unnamed: C8.1, R.GAIN.1
unnamed: C9.2, IC1.2 (-IN), R9.1
unnamed: C10.2, C11.1, IC1.1 (OUT), R9.2
unnamed: C11.2, C12.1, TRIM2.1 (A)
unnamed: C12.2, TRIM1.1 (A)
unnamed: IC2.7 (I), R10.1, TRIM1.2 (S), TRIM2.2 (S)
unnamed: IC2.6 (O), R10.2, R11.1
unnamed: IC2.3 (I), R11.2, R12.1
unnamed: IC2.2 (O), R12.2, R13.1
unnamed: C13.1, IC2.5 (I), R13.2, R14.1
unnamed: C13.2, C14.1, IC2.4 (O), R14.2
unnamed: C14.2, C16.2, R15.2, R18.1
unnamed: R18.2, R19.1, TONE.3
unnamed: C16.1, R17.2
unnamed: C17.2, R16.2, R17.1, TONE.1
unnamed: C15.2, R15.1, R16.1
unnamed: B.LEVEL.1, R.LEVEL.3, TONE.2
unnamed: IC1.5 (+IN), IC1.7 (OUT)
OUT: X1.2
VA: C2.2, C4.+, IC2.1 (VDD), IC2.9 (I), IC2.11 (I), IC2.14 (I), R2.2
VB: C3.2, C5.+, IC1.3 (+IN), IC1.6 (-IN), IC1.8 (V+), R3.2, R4.2
VR: C1.+, Q1.3 (D), R1.2, R2.1, R3.1

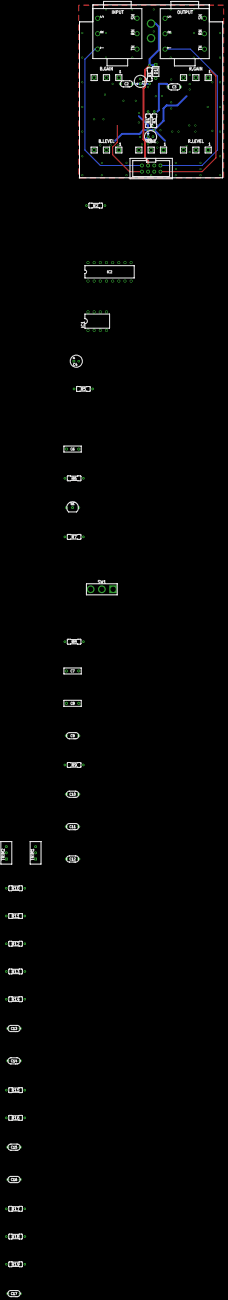
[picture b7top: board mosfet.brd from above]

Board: 2 copper layers, 59.0 x 71.3 mm, 53 parts (1 on the bottom side), 31 nets.

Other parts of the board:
U$1: 125B_PCB
